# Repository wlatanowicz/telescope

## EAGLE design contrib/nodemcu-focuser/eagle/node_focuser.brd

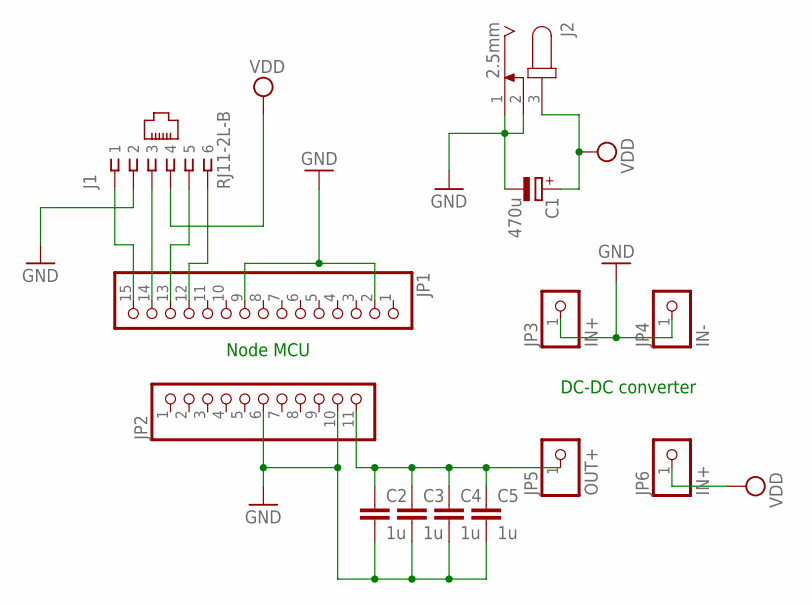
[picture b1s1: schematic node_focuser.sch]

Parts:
C1: 470u; E3,5-8
C2, C3, C4, C5: 1u; C5B3
J1: RJ11-2L-B; RJ11-NO_SHIELD
J2: 2.5mm; SPC4077
JP1: PINHD-1X15; 1X15
JP2: PINHD-1X11; 1X11
JP3, JP6: IN+; 1X01
JP4: IN-; 1X01
JP5: OUT+; 1X01

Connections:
GND: C1.-, C2.2, C3.2, C4.2, C5.2, J1.2, J2.1, J2.2, JP1.2, JP1.9, JP2.6, JP2.10, JP3.1, JP4.1
unnamed: J1.1, JP1.15
unnamed: J1.3, JP1.14
unnamed: J1.5, JP1.13
unnamed: J1.6, JP1.12
unnamed: C2.1, C3.1, C4.1, C5.1, JP2.11, JP5.1
VDD: C1.+, J1.4, J2.3, JP6.1

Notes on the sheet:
Node MCU
DC-DC converter

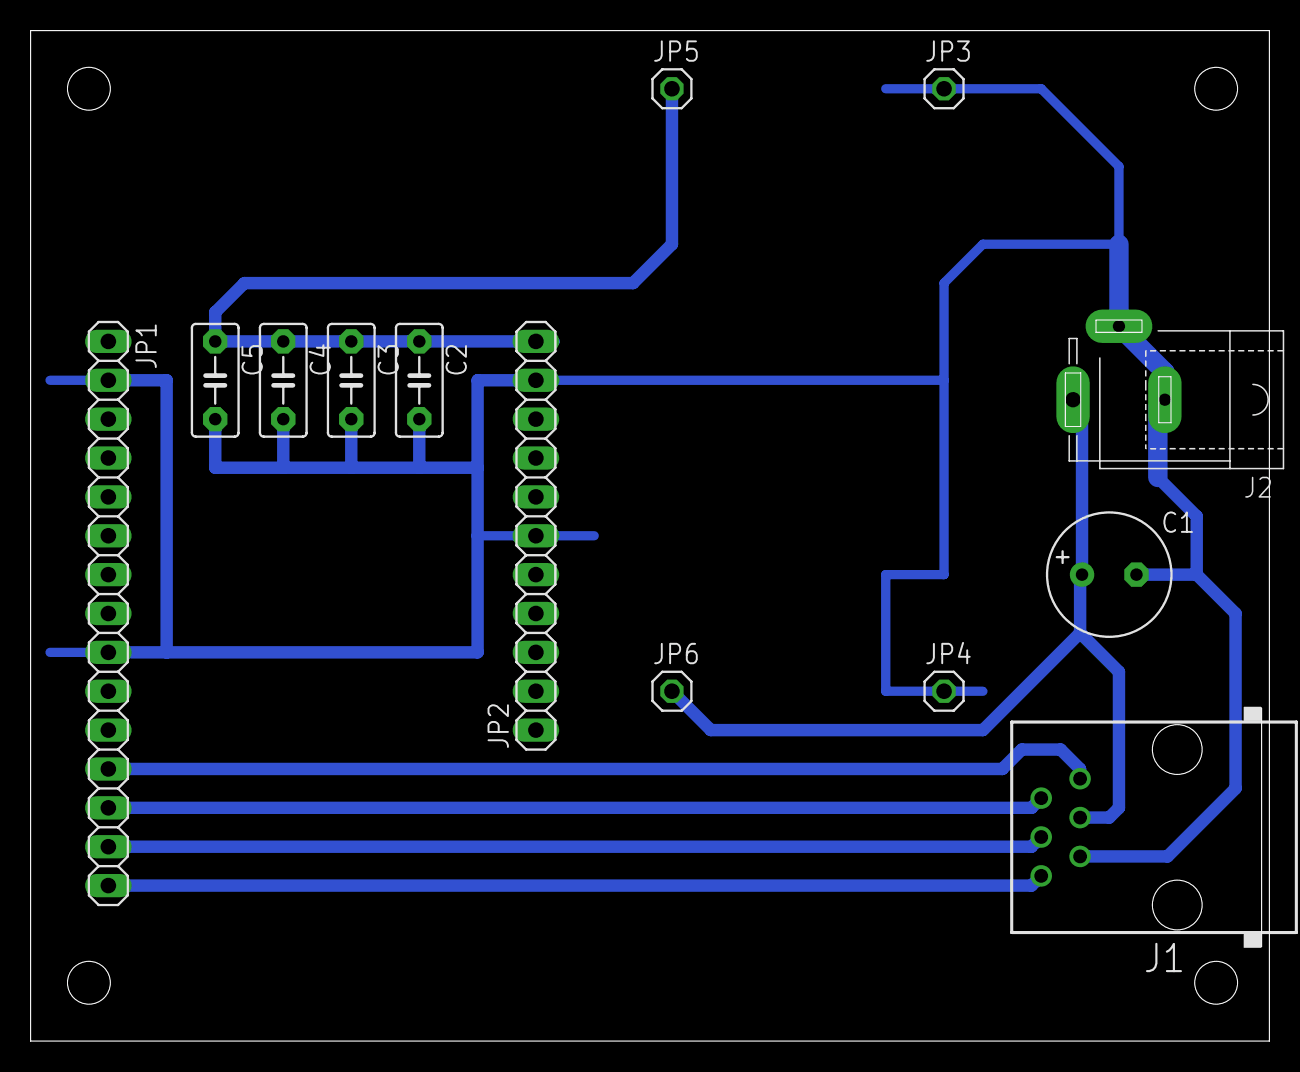
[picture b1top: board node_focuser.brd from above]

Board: 2 copper layers, 80.9 x 66.0 mm, 13 parts (0 on the bottom side), 7 nets.

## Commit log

2016-11-03 hsv to rgb
2016-11-03 extract factory
2016-11-03 work
2016-11-18 command
2016-11-18 telescope commands
2016-11-18 coords padding
2016-11-18 diag
2016-11-19 shorter time
2016-11-19 add var to gitignore
2016-12-01 no message
2016-12-04 esp8266 focuser firmware
2016-12-05 auto speed
2016-12-08 remove temp file before capture
2016-12-09 serializer
2016-12-09 dummy camera
2016-12-11 firmware
2016-12-11 speed fix + stop motor on idle
2016-12-11 error handlig, proper POST, PATCH, DELETE handling
2016-12-11 code cleanup
2016-12-11 static ip
2016-12-11 pcb design and schematic diagram
2016-12-13 focus measure
2016-12-13 refactor
2016-12-14 response http headers
2016-12-14 work on focuser
2016-12-14 commands
2016-12-17 autofocus: work in progress
2016-12-17 GdCamera for AutoFocus
2016-12-17 hardware simulators
2016-12-17 additional autofocus test
2016-12-18 camera simulator with focus simulation
2016-12-18 work on autofocus
2016-12-21 work on remote access
2016-12-22 autofocus work in progress
2016-12-23 auto focus report generator
2016-12-23 report font
2016-12-23 work on auto focuser report
2016-12-23 some logging
2016-12-23 remote telescope
2016-12-25 telescope service fix
2016-12-25 simulate device action time
2016-12-25 better logging
2016-12-26 better colors for unknown device
2016-12-27 base64 as transport for images from remote camera
2016-12-27 null mimetypes
2016-12-27 use annotation
2016-12-27 logging for node focuser
2016-12-27 load annotations
2016-12-27 device config
2016-12-27 expose without settings
2016-12-27 types in binaryimage
2016-12-28 focus measure command
2016-12-28 fix mount serial connections
2016-12-29 serial port setup
2016-12-29 node network settings
2016-12-30 default devices
2016-12-30 setup camera command
2017-01-01 logging and json response on error in api
2017-01-01 default devices in config parameters
2017-01-01 typo in log
2017-01-01 cleanup autofocus
2017-01-01 remove dummy hardware
2017-01-01 camera settings
2017-01-01 read current camera setting
2017-01-01 camera setup command
2017-01-01 more logging in autofocus
2017-01-01 logger for camera setup
2017-01-01 mimetype autodetection, automatic file extensions
2017-01-02 different try count per iteration
2017-01-02 fix behaviour in constant focus areas
2017-01-02 excpetion on non-measurable image
2017-01-02 custom log color scheme
2017-01-03 exception on end-points in autofocus
2017-01-08 fix handling tries option
2017-01-08 refactor: extract finding next min and max positions
2017-01-17 log verbosity levels
2017-01-18 refactor configuration
2017-01-18 job manager and log handler
2017-01-19 autofocus job
2017-01-20 rename Job namespace
2017-01-20 fix bin image serialization
2017-01-20 typo
2017-01-22 work on job manager
2017-01-22 job result storage
2017-01-22 proper result store + better default ids
2017-01-22 rpc controller
2017-01-23 phpunit logging
2017-01-23 hardware controller tests
2017-01-23 fix exposure in camera controller
2017-01-23 rpc controller test
2017-01-27 better jpeg recognision
2017-01-30 stellarium server telescope connector
2017-01-30 focuser and telescope position jobs
2017-01-30 test style
2017-01-30 telescope tolerance
2017-01-31 test generator - to extract to separate repo in the future
2017-01-31 devbundle extracted to separate repo
2017-01-31 skip test
2017-01-31 camera expose job
2017-01-31 camera expose job - cli
2017-01-31 configure camera expose job in provider
2017-01-31 test star measure
2017-02-01 better measure test
2017-02-01 more measure tests
2017-02-01 work on job status
2017-02-01 work on jobs
2017-02-04 fix tests and params mappings
2017-02-04 alternative routes for job start
2017-02-04 position persistance in focuser simulator
2017-02-04 fix job api test
2017-02-05 job tests
2017-02-06 frontend initial commit
2017-02-06 work on zoomable image preview
2017-02-08 work on frontend - autofocus
2017-02-08 job result info
2017-02-08 jsonrpc compilant response
2017-02-08 jsonrpc compilant response - test
2017-02-08 read focuser sim initial position
2017-02-11 autofocus on frontend
2017-02-11 autofocus job fixes
2017-02-11 better ease-in-and-out when updating position
2017-02-11 exception on file read error
2017-02-11 phone remote app
2017-02-11 pass target position via post body or get params
2017-02-11 better responsiveness
2017-02-11 slider as speed selector
2017-02-11 better button arrangement
2017-02-11 some ios configs
2017-02-11 better ux with slider
2017-02-12 allow speed adjusting via get parameter
2017-02-12 tomek.js as npm package
2017-02-12 npm modules
2017-02-12 configure speed and range
2017-02-18 update gulpfile for latest tomek
2017-02-23 spectrum factory
2017-02-23 work on radio scanner
2017-02-24 ensure dir exists before creating a file
2017-02-24 extract factories from data objects
2017-03-27 remove unused use
2017-03-27 remove not-yet-implemented command
2017-03-28 migrate frontend to typescript
2017-03-29 work on aiming interface
2017-05-03 adapt to prefix-less framework version
2017-05-06 work on image/position calibration, unit tests
2017-05-09 better service definition
2017-05-10 focuser app: update to typescript
2017-05-14 symlink to frontend
2017-05-14 remote dark skin
2017-05-14 post-merge fix
2017-05-14 non-bulb mode for sony camera (requires libgphoto2 >= 2.5.13)
2017-05-14 fix exposure time type
2017-05-15 fix exposure times
2017-05-15 proper ignore list for phone remote
2017-05-15 correct focuser ip address + some cleanup
2017-05-15 bettery level check
2017-07-01 fix sony exposure time string factory test
2017-07-01 fix type
2017-07-01 use imagick image factory in camera simulator
2017-07-01 silent errors
2017-08-11 Create Dockerfile
2017-08-16 fix building issues
2017-08-17 api for listing available hardware
2017-08-19 work on camera control gui
2017-09-28 FIx default rest endpoint for docker
2017-09-28 use php 7.1
2017-10-02 Jenkinsfile
2017-10-02 Fetch multiple formats from camera
2017-10-04 Some additional testing config
2017-11-07 WIP: support for nikon
2017-11-07 WIP: refactor get rid of imagick-camera-thing
2017-11-07 camera simulator based on real data
2017-11-07 Fix af report generator
2017-11-08 automated config load depending on os
2017-11-08 refactor + nef type detection
2017-11-08 linear regression algorithm
2017-11-08 Double linear regression autofocus algorithm
2017-11-08 better passing options to measure
2017-11-09 extensions in lower case
2017-11-09 error when no images fetched from camera (ie. wrong filename)
2017-11-11 Better result in lin-reg af
2017-11-11 span based measurement
2017-11-11 optimize docker
2017-11-11 Algorithm selection in front, fix marker and star selection
2017-11-12 measure testing command
2017-11-12 Point distance measure
2017-11-22 Long exposures on Nikon using GPIO connected IR remote
2017-11-22 Fix getting info
2017-11-25 fix ir remote transmit time
2017-11-25 WIP: repositioning
2017-11-30 WIP: scope repositioning
2017-12-28 Docker for building FocuserPhoneRemote for ios
